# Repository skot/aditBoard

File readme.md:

## aditBoard

The aditBoard is a USB adapter for Bitmain hashboards. It's based on the RaspberryPi RP2040. All of the hashboard functions (especially mining) can be utilized over USB. AditBoard will work with a PC, laptop, Raspberry Pi, or new controlboards like the [LibreBoard](libreboard.org) from [The 256 Foundation](https://256foundation.org)

- Manufacturing Files are included to support PCBA from [JLCPCB](https://jlcpcb.com)
- For example fan and PSU control from a Raspberry Pi check out the [AntHat](https://github.com/skot/anthat)
- Preliminary [firmware](https://github.com/The-256-Foundation/ember-one-firmware) for the aditBoard

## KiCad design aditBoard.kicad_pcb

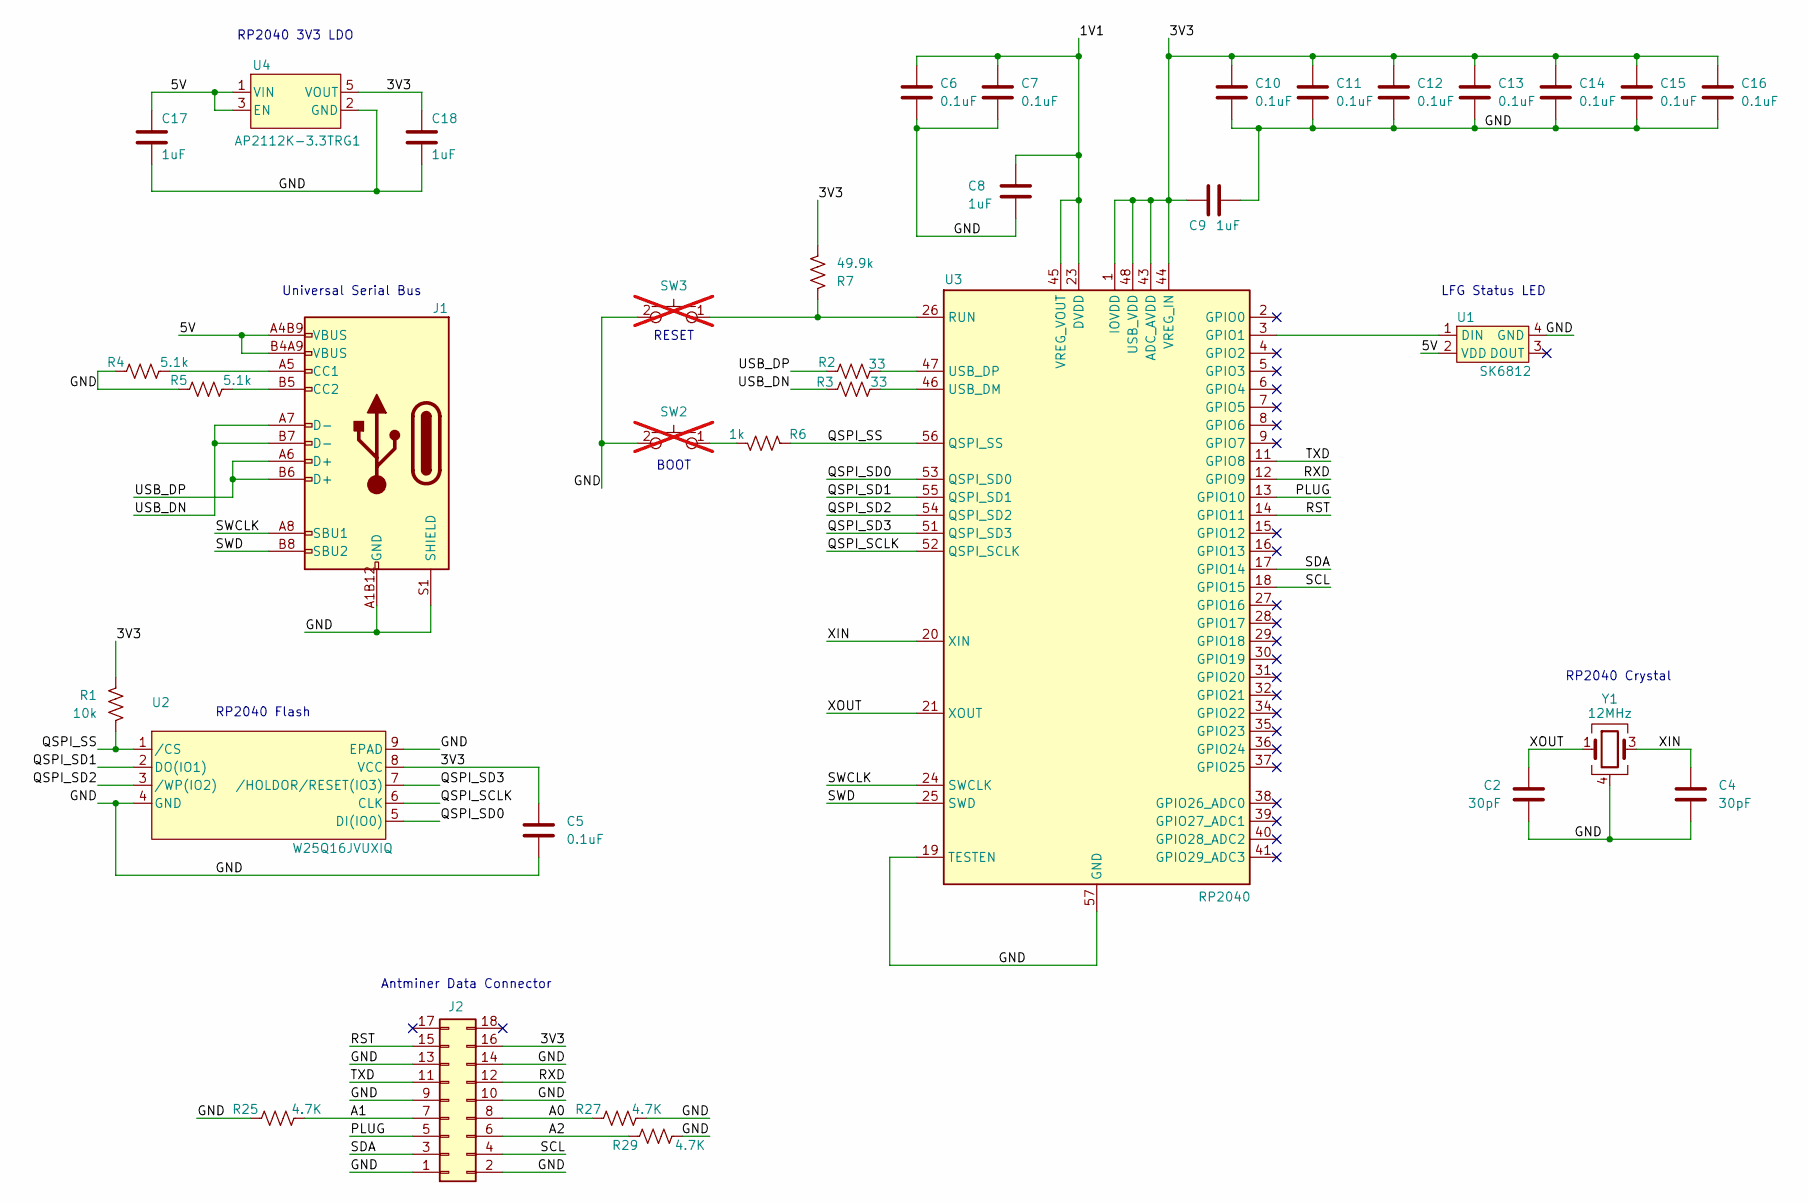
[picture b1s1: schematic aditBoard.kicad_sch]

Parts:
C2, C4: 30pF; C_0402_1005Metric; PARTNO 0402CG300J500NT; JLC Part Basic Part
C5, C6, C7, C10, C11, C12, C13, C14, C15, C16: 0.1uF; C_0402_1005Metric; PARTNO CL05B104KB54PNC; JLC Part Basic Part
C8, C9: 1uF; C_0402_1005Metric; PARTNO CL05A105KA5NQNC; JLC Part Basic Part
C17, C18: 1uF; C_0402_1005Metric; PARTNO CL05A105KA5NQNC; LCSC C52923
J1: USB_C_Receptacle_USB2.0; USB_C_Receptacle_GCT_USB4105-xx-A_16P_TopMnt_Horizontal; PARTNO USB4105-GF-A; LCSC C2988369
J2: Hashboard0; PinHeader_2x09_P2.00mm_Horizontal; PARTNO PM200-2-09-W-4.3; LCSC C3012192
R1: 10k; R_0402_1005Metric; PARTNO 0402WGF1002TCE; LCSC C25744
R2, R3: 33; R_0402_1005Metric; PARTNO 0402WGF330JTCE; JLC Part Basic Part
R4, R5: 5.1k; R_0402_1005Metric; PARTNO RMCF0402JT5K10; LCSC C25905
R6: 1k; R_0402_1005Metric; PARTNO RC0402FR-071KL; LCSC C106235
R7: 49.9k; R_0402_1005Metric; PARTNO RC0402FR-0749K9L; LCSC C137969
R25, R27, R29: 4.7K; R_0402_1005Metric; PARTNO RC0805FR-074K7L; LCSC C25900
SW2, SW3: GT-TC029B-H025-L1N; SW_CS1213AGF260_CRS; PARTNO CS1213AGF260; LCSC C5578986; not fitted
U1: SK6812; LED-SMD_4P-L4.0-W1.6-L; PARTNO SK6812SIDE-A-RVS; LCSC C2890037
U2: W25Q16JVUXIQ; USON8_L2.0-W3.0-P0.50-BL-EP; PARTNO W25Q16JVUXIQ; LCSC C2843335
U3: RP2040; QFN-56-1EP_7x7mm_P0.4mm_EP3.2x3.2mm; PARTNO RP2040; LCSC C2040
U4: AP2112K-3.3TRG1; SOT-25-5_L2.9-W1.6-P0.95-LS2.8-BL; PARTNO AP2112K-3.3TRG1; LCSC C51118
Y1: 12MHz; OSC-SMD_4P-L3.2-W2.5-BL; PARTNO X322512MSB4SI; LCSC C9002

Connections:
/1V1: C6.2, C7.2, C8.2, U3.23 (DVDD), U3.45 (VREG_VOUT), U3.50 (DVDD)
/3V3: C5.2, C9.1, C10.2, C11.2, C12.2, C13.2, C14.2, C15.2, C16.2, C18.1, J2.16, R1.1, R7.2, U2.8 (VCC), U3.1 (IOVDD), U3.10 (IOVDD), U3.22 (IOVDD), U3.33 (IOVDD), U3.42 (IOVDD), U3.43 (ADC_AVDD), U3.44 (VREG_IN), U3.48 (USB_VDD), U3.49 (IOVDD), U4.5 (VOUT)
/5V: C17.1, J1.A4B9 (VBUS), J1.B4A9 (VBUS), U1.2 (VDD), U4.1 (VIN), U4.3 (EN)
/A0: J2.8, R27.1
/A1: J2.7, R25.2
/A2: J2.6, R29.1
/GND: C2.1, C4.1, C5.1, C6.1, C7.1, C8.1, C9.2, C10.1, C11.1, C12.1, C13.1, C14.1, C15.1, C16.1, C17.2, C18.2, J1.A1B12 (GND), J1.B1A12 (GND), J1.S1 (SHIELD), J2.1, J2.2, J2.9, J2.10, J2.13, J2.14, R4.1, R5.1, R25.1, R27.2, R29.2, SW2.2, SW3.2, U1.4 (GND), U2.4 (GND), U2.9 (EPAD), U3.19 (TESTEN), U3.57 (GND), U4.2 (GND), Y1.2, Y1.4
/PLUG: J2.5, U3.13 (GPIO10)
/QSPI_SCLK: U2.6 (CLK), U3.52 (QSPI_SCLK)
/QSPI_SD0: U2.5 (DI(IO0)), U3.53 (QSPI_SD0)
/QSPI_SD1: U2.2 (DO(IO1)), U3.55 (QSPI_SD1)
/QSPI_SD2: U2.3 (/WP(IO2)), U3.54 (QSPI_SD2)
/QSPI_SD3: U2.7 (/HOLDOR/RESET(IO3)), U3.51 (QSPI_SD3)
/QSPI_SS: R1.2, R6.1, U2.1 (/CS), U3.56 (QSPI_SS)
/RST: J2.15, U3.14 (GPIO11)
/RXD: J2.12, U3.12 (GPIO9)
/SCL: J2.4, U3.18 (GPIO15)
/SDA: J2.3, U3.17 (GPIO14)
/SWCLK: J1.A8 (SBU1), U3.24 (SWCLK)
/SWD: J1.B8 (SBU2), U3.25 (SWD)
/TXD: J2.11, U3.11 (GPIO8)
/USB_DN: J1.A7 (D-), J1.B7 (D-), R3.1
/USB_DP: J1.A6 (D+), J1.B6 (D+), R2.1
/XIN: C4.2, U3.20 (XIN), Y1.3
/XOUT: C2.2, U3.21 (XOUT), Y1.1
unnamed: J1.A5 (CC1), R4.2
unnamed: J1.B5 (CC2), R5.2
unnamed: R6.2, SW2.1
unnamed: U1.1 (DIN), U3.3 (GPIO1)
unnamed: R7.1, SW3.1, U3.26 (RUN)
unnamed: R3.2, U3.46 (USB_DM)
unnamed: R2.2, U3.47 (USB_DP)

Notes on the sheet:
Antminer Data Connector
LFG Status LED
RESET
RP2040 Flash
RP2040 Crystal
RP2040 3V3 LDO
BOOT
Universal Serial Bus

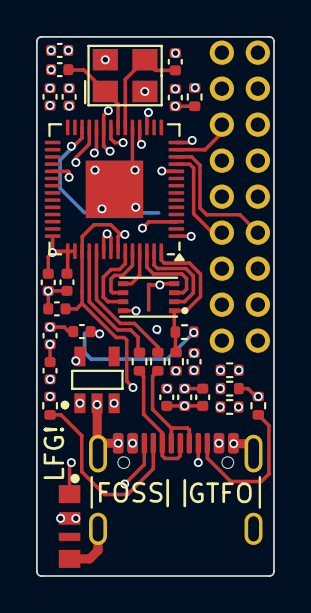
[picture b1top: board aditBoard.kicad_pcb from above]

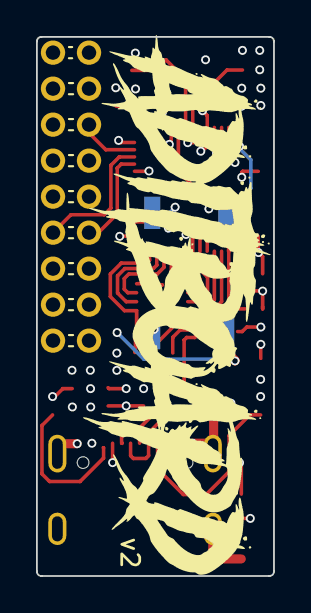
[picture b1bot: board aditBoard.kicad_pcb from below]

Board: 6 copper layers, 13.2 x 30.0 mm, 35 parts (2 on the bottom side), 32 nets.

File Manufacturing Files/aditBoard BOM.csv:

Qty,Reference,Value,PARTNO,LCSC
2,C2 C4,30pF,0402CG300J500NT,C1570
10,C5 C6 C7 C10 C11 C12 C13 C14 C15 C16,0.1uF,CL05B104KB54PNC,C307331
4,C8 C9 C17 C18,1uF,CL05A105KA5NQNC,C52923
2,R2 R3,33,0402WGF330JTCE,C25105
1,R6,1k,RC0402FR-071KL,C106235
1,U1,SK6812,SK6812SIDE-A-RVS,C2890037
1,U3,RP2040,RP2040,C2040
1,U4,AP2112K-3.3TRG1,AP2112K-3.3TRG1,C51118
1,Y1,12MHz,X322512MSB4SI,C9002
1,J2,Hashboard0,PM200-2-09-W-4.3,C3012192
1,J1,USB_C_Receptacle_USB2.0,USB4105-GF-A,C2988369
1,U2,W25Q16JVUXIQ,W25Q16JVUXIQ,C2843335
1,R1,10k,0402WGF1002TCE,C25744
2,R4 R5,5.1k,RMCF0402JT5K10,C25905
1,R7,49.9k,RC0402FR-0749K9L,C137969
3,R25 R27 R29,4.7K,RC0805FR-074K7L,C25900

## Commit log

2024-03-26 initial Import
2024-03-27 pretty much routed
2024-03-27 added artwork, DRC, LCSC BOM
2024-03-27 add readme
2024-03-27 adding checked gerbers
2024-04-19 adding ibom
2025-01-20 Switched SPI Flash part number for #1
2025-02-13 updated render to reflect the correct side for soldering the data connector.
2025-02-13 switched a lot of KiCad parts to STEP from WRL. This seems to make the board STEP export better.
2025-06-09 update to KiCad v9
2025-06-09 added BOM and cpl
2025-06-10 bumped version to 2. added RGB LED
2025-06-10 switched to 6L. Routed LED
2025-06-10 Added option for BOOT and RESET buttons. added gerbers and BOM
2025-06-10 added JLCPCB format CPL file
2025-06-10 updated BOM and CPL for JLCPCB
2025-06-10 update render
2025-06-10 gitignore update
